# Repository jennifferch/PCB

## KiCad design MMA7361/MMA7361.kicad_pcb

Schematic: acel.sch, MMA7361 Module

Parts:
C1, C3, C5: 3.3nf; C_0805_2012Metric_Pad1.15x1.40mm_HandSolder
C2, C6: 1 µF; C_0805_2012Metric_Pad1.15x1.40mm_HandSolder
C4, C7: 470 µF; C_0805_2012Metric_Pad1.15x1.40mm_HandSolder
D1: LED; LED_0805_2012Metric_Pad1.15x1.40mm_HandSolder
F1, F2, F3: Fiducial; Fiducial_0.5mm_Dia_1mm_Outer
J1, J2: Conn_01x05; PinHeader_1x05_P1.00mm_Vertical
R1: 1 K; R_0805_2012Metric_Pad1.15x1.40mm_HandSolder
U1: RT9161; SOT-23-5_HandSoldering
U2: MMA7361L; QFN-16

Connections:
+5V: C2.1, C4.1, U1.3 (VIN), U1.4 (VIN/EN)
/MMA 7361 Module/Og-Detect: J2.5, U2.9
/MMA 7361 Module/SelfTest: J1.5, U2.13
/MMA 7361 Module/Sleep: J2.4, U2.7
/MMA 7361 Module/g-Select: J1.4, U2.10
GND: C1.1, C2.2, C3.1, C4.2, C5.1, C6.2, C7.2, D1.1 (K), J1.3, J2.1, J2.2, J2.3, U1.2 (GND), U2.5
unnamed: C1.2, U2.4
unnamed: C3.2, U2.2
unnamed: C5.2, U2.3
unnamed: D1.2 (A), R1.1
VCC: C6.1, C7.1, J1.2, R1.2, U1.1 (VOUT), U1.5 (VOUT), U2.6

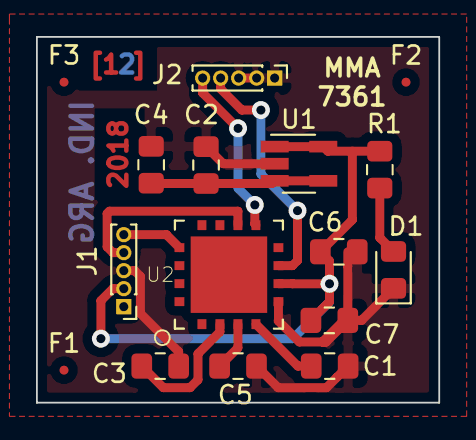
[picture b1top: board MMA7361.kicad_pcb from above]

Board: 2 copper layers, 22.4 x 20.3 mm, 16 parts (0 on the bottom side), 11 nets.

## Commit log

2018-10-01 The documentations has been added
2018-10-14 The last changes has been added
2018-10-18 The change of component have been added
2018-10-25 The Schematic have been fixed
2018-10-26 More changes
2018-10-29 The last change have been added
2018-11-02 the files have been fixed
2018-11-14 New changes have been added
2018-11-15 The last version have been added
